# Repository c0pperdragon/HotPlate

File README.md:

# HotPlate

Cheap DIY solution to make a heater for hot-plate soldering.

## Operating instructions

1. Plug the device to a common 12V DC power source that is able to provide 5 ampere.
2. Place the object to be soldered on the heater plate.
3. Switch on the heater with the red power button.
4. Select a target temperature (the "Set" value on the display) with the potentiometer.
5. When the solder is molten enough, turn off the heater with the red button. Note that
there is no support to automatically follow a temperature profile.

To switch the device between centigrade and fahrenheit, press the power button more than 
3 seconds when turning it on.

## Data shown on the display

* Set: Selected target temperature
* Temp: Temperature as measured

The numbers in the bottom area are used to understand the internal working and show the 
following things: 
* Duty cycle of the heater
* Supply voltage 
* Current through the top heater trace

## Theory of operation

The heater plate contains two copper traces (one at the top and one at the bottom) that can individually
be connected to the supply voltage. These traces have a resistance of about 3.5 ohm each (within
manufacturing tolerances) and will produce the heat for the process. For fine control of the output power,
the controller circuit will quickly turn each heater trace on and off.

To receive feeedback about the current temperature, the controller circuit contains a Hall-effect sensor
to monitor the electric current running through the top heater trace. Combined with the 
voltage that is also monitored, the resistance of this trace can be computed. As the specific resistance of
copper changes with temperature, the current temperature can be computed. 

Note that due to tolerances in PCB manufacturing and in the electronic parts, the temperature measurement
may be not very precise. You will need to experimentally find the best temperature setting for your specific application.

## Replacement heater plate

The repeated thermal stress on the heater will probably cause it to get damaged eventually. In this case
it is quite easy to have a replacement PCB made using the [Gerber files](heater/gerber).
As you will probably get multiple parts from your manufacturer, this should then last for a considerable 
time. 
You can also just turn over the heater plate if the top surface gets scratched or is otherwise worn out,
so you can continue to use it.

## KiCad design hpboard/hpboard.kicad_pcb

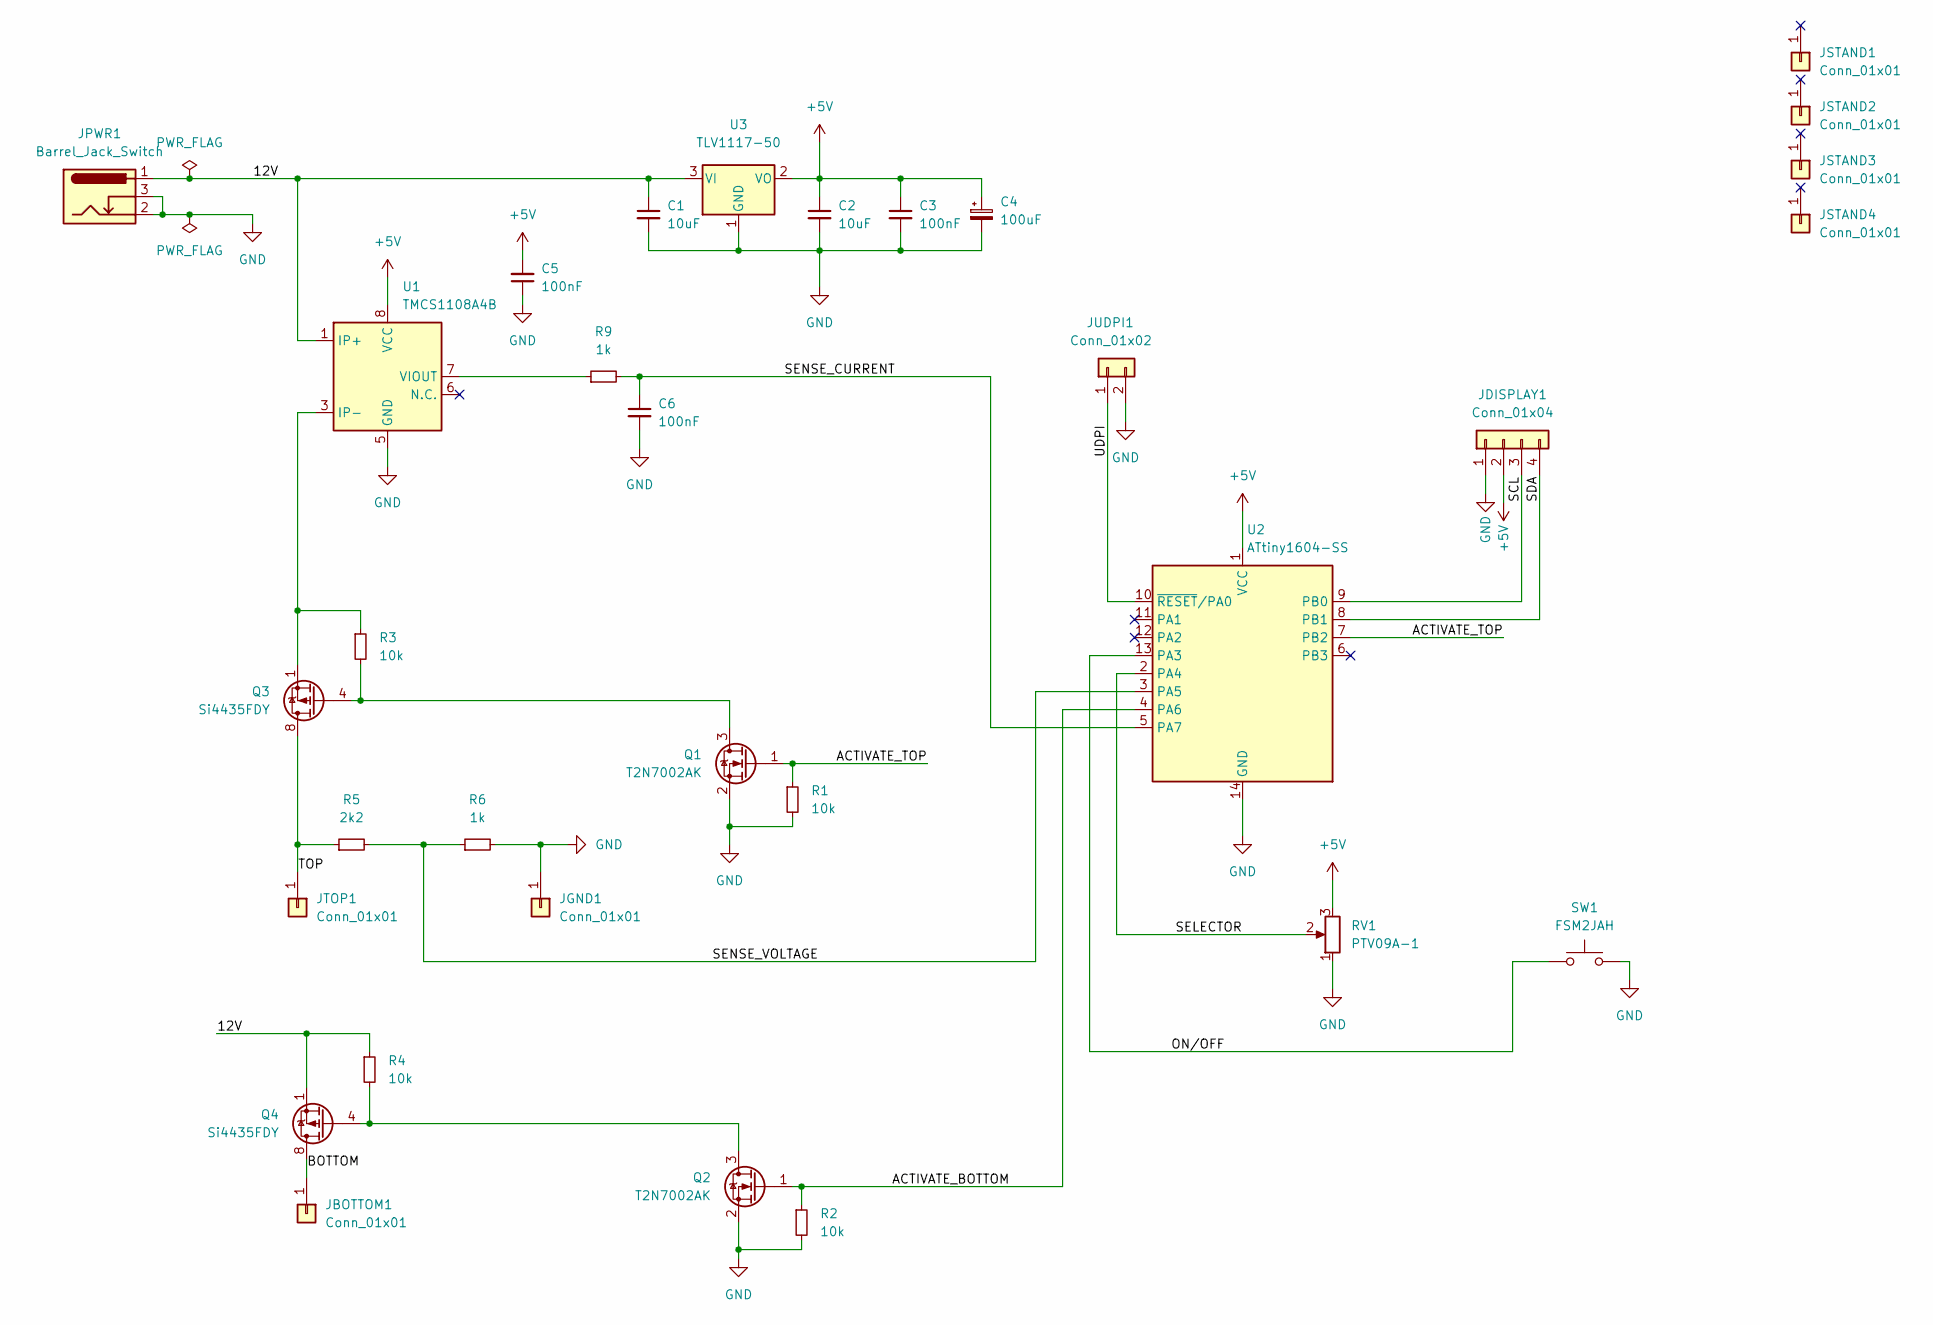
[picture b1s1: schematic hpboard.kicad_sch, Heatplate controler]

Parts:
C1, C2: 10uF; C_0805_2012Metric_Pad1.18x1.45mm_HandSolder
C3, C5, C6: 100nF; C_0603_1608Metric_Pad1.08x0.95mm_HandSolder
C4: 100uF; CP_EIA-3528-21_Kemet-B_Pad1.50x2.35mm_HandSolder
JBOTTOM1: Conn_01x01; MountingHole_3.2mm_Large
JDISPLAY1: Conn_01x04; PinHeader_1x04_P2.54mm_Vertical
JGND1: Conn_01x01; MountingHole_3.2mm_Large
JPWR1: Barrel_Jack_Switch; BarrelJack_Horizontal
JSTAND1, JSTAND2, JSTAND3, JSTAND4: Conn_01x01; MountingHole_3.2mm_Large
JTOP1: Conn_01x01; MountingHole_3.2mm_Large
JUDPI1: Conn_01x02; PinHeader_1x02_P2.54mm_Vertical
Q1, Q2: T2N7002AK; SOT-23
Q3, Q4: Si4435FDY; SOIC-8_3.9x4.9mm_P1.27mm
R1, R2, R3, R4: 10k; R_0805_2012Metric_Pad1.20x1.40mm_HandSolder
R5: 2k2; R_0805_2012Metric_Pad1.20x1.40mm_HandSolder
R6, R9: 1k; R_0805_2012Metric_Pad1.20x1.40mm_HandSolder
RV1: PTV09A-1; Potentiometer_Bourns_PTV09A-1_Single_Vertical
SW1: FSM2JAH; SW_PUSH_6mm
U1: TMCS1108A4B; SOIC-8_3.9x4.9mm_P1.27mm
U2: ATtiny1604-SS; SOIC-14_3.9x8.7mm_P1.27mm
U3: TLV1117-50; SOT-223-3_TabPin2

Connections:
+5V: C2.1, C3.1, C4.1, C5.2, JDISPLAY1.2, RV1.3, U1.8 (VCC), U2.1 (VCC), U3.2 (VO)
/12V: C1.1, JPWR1.1, Q4.1 (S), Q4.2 (S), Q4.3 (S), R4.1, U1.1 (IP+), U1.2 (IP+), U3.3 (VI)
/ACTIVATE_BOTTOM: Q2.1 (G), R2.1, U2.4 (PA6)
/ACTIVATE_TOP: Q1.1 (G), R1.1, U2.7 (PB2)
/BOTTOM: JBOTTOM1.1, Q4.5 (D), Q4.6 (D), Q4.7 (D), Q4.8 (D)
/ON/OFF: SW1.1, U2.13 (PA3)
/SCL: JDISPLAY1.3, U2.9 (PB0)
/SDA: JDISPLAY1.4, U2.8 (PB1)
/SELECTOR: RV1.2, U2.2 (PA4)
/SENSE_CURRENT: C6.1, R9.2, U2.5 (PA7)
/SENSE_VOLTAGE: R5.2, R6.1, U2.3 (PA5)
/TOP: JTOP1.1, Q3.5 (D), Q3.6 (D), Q3.7 (D), Q3.8 (D), R5.1
/UDPI: JUDPI1.1, U2.10 (~RESET/PA0)
GND: C1.2, C2.2, C3.2, C4.2, C5.1, C6.2, JDISPLAY1.1, JGND1.1, JPWR1.2, JPWR1.3, JUDPI1.2, Q1.2 (S), Q2.2 (S), R1.2, R2.2, R6.2, RV1.1, SW1.2, U1.5 (GND), U2.14 (GND), U3.1 (GND)
unnamed: Q1.3 (D), Q3.4 (G), R3.2
unnamed: Q2.3 (D), Q4.4 (G), R4.2
unnamed: Q3.1 (S), Q3.2 (S), Q3.3 (S), R3.1, U1.3 (IP-), U1.4 (IP-)
unnamed: R9.1, U1.7 (VIOUT)

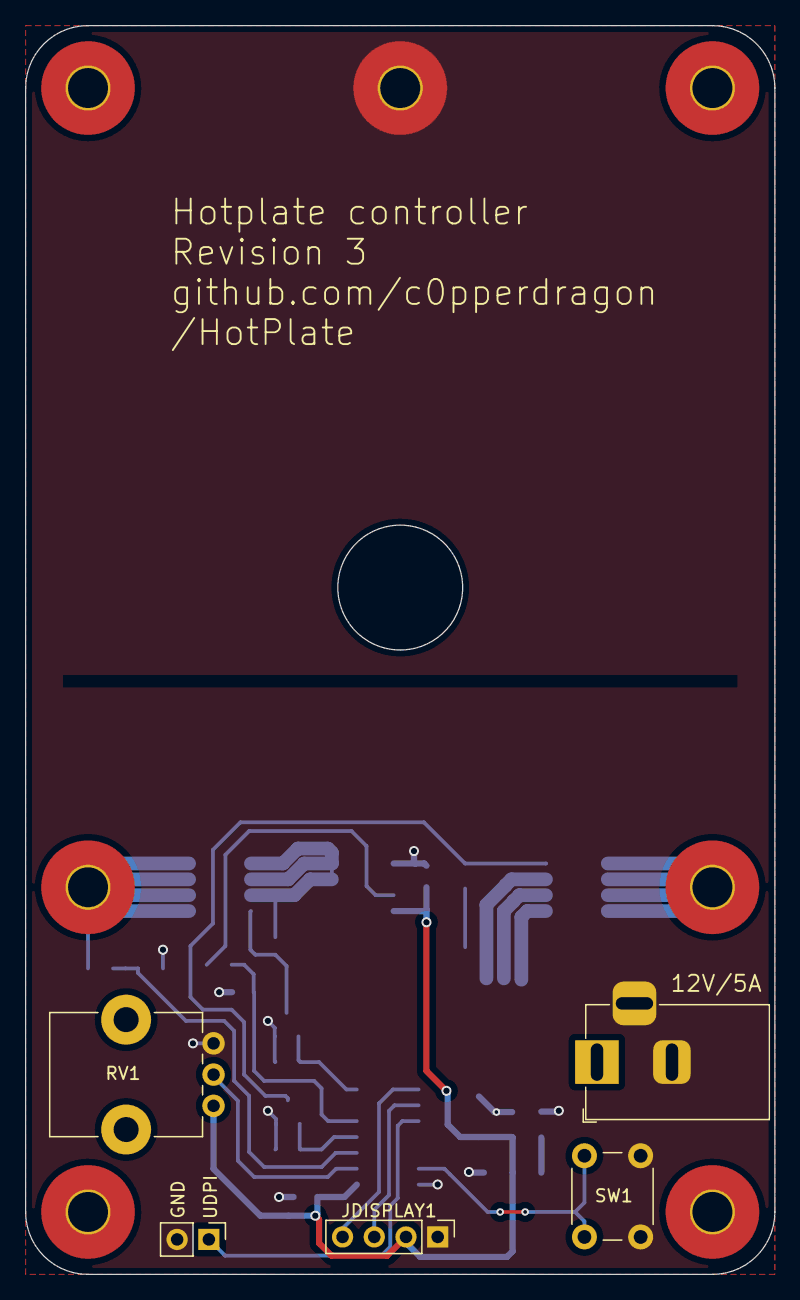
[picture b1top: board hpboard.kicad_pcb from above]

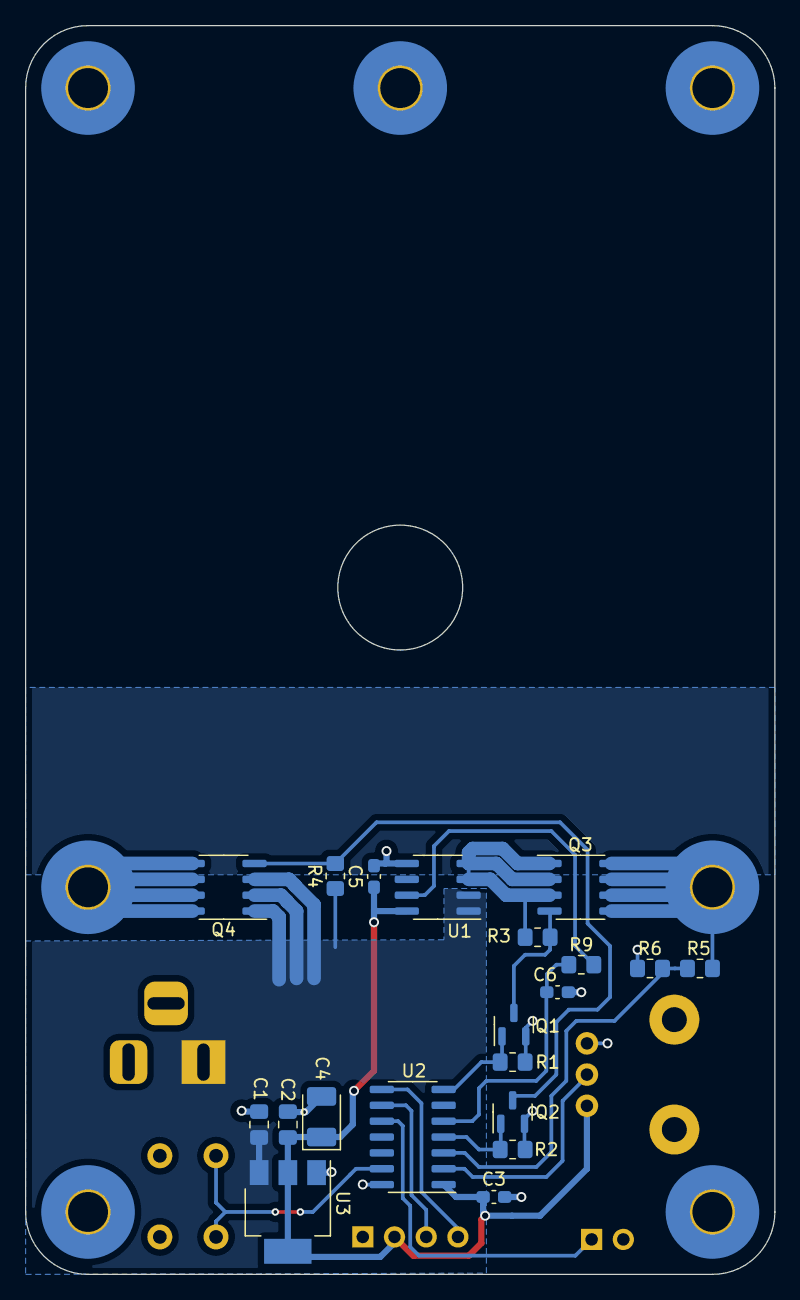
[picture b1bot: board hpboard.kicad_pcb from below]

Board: 2 copper layers, 60.0 x 100.0 mm, 32 parts (20 on the bottom side), 18 nets.

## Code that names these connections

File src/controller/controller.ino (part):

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#include "oled.h"

// -- defining pins
#define ACTIVATE_TOP     PIN_PB2
#define ACTIVATE_BOTTOM  PIN_PA6   
#define SELECTOR         PIN_PA4
#define ONOFF            PIN_PA3
#define SENSE_VOLTAGE    PIN_PA5
#define SENSE_CURRENT    PIN_PA7

// -- state of the hardware
volatile bool standby = true;
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// -- configure pins and set up interrupt
void setup() 
{
  pinMode(ACTIVATE_TOP, OUTPUT);
  digitalWrite(ACTIVATE_TOP, LOW);
  pinMode(ACTIVATE_BOTTOM, OUTPUT);
  digitalWrite(ACTIVATE_BOTTOM, LOW);
  pinMode(SELECTOR, INPUT);
  pinMode(ONOFF, INPUT_PULLUP);
  pinMode(SENSE_VOLTAGE, INPUT);
  pinMode(SENSE_CURRENT, INPUT);

  Wire.begin(); 
  Wire.setClock(50000);
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
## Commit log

2023-01-19 Design schematics
2023-01-20 Design heating plate
2023-01-20 Add some space between ICs
2023-02-07 Start firmware development
2023-02-12 Codeing
2023-02-14 implement PI-regulation
2023-02-20 Less noise in current sensing. Faster regulation.
2023-02-21 Support Fahrenheit display Fix silkscreen on heater
2023-02-22 Turn on simultanious surface heating earlier.
2023-02-22 Remove unnecessary pull-ups
2023-02-24 Improve temperature control
2023-03-02 Calibrate temperature sensing
2023-03-04 Documentation
2023-03-04 Fix link to gerber
2023-03-09 Change text on heater plate
2023-03-09 Rework PCB for better soldering
2023-03-09 Update schematic PDF
2023-06-23 Add hole to PCB to allow the hotplate to SMD-solder its own clone. Switch GND and VCC on display module to support slimmer and more common variant
2023-08-24 Add auto-off feature
2024-04-30 Fine-tune temperature sensing
